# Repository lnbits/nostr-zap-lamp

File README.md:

# Nostr Zap Lamp

Get a visual "Zap!"" when someone zaps you or anyone on Nostr.

The Nostr Zap Lamp flashes when a relay broadcasts a Nostr event of kind 9735. You can set the lamp to flash zaps sent to a specific npub, or any npub on nostr.

The number of flashes corresponds to the number of digits in the number of sats sent. i.e. 3 sats will result in 1 flash, 152 sats will result in 3 flashes, 1001 sats will result in 4 flashes.

[Buy a pre-assembled or complete Zap Lamp kit on the LNbits shop](https://shop.lnbits.com/product/nostr-zap-lamp)

# Features

+ Show a signal when a zap is sent to one or all nostr npubs
+ Background brightness control
+ Easily configure to use your own nostr relay
+ Simple configuration to work with any npub

## Parts
+ [LED "Neon" lamp](https://www.amazon.co.uk/YIVIYAR-Lightning-Battery-Bedroom-Christmas/dp/B08K4SCVKQ)
+ An ESP32 dev board
+ USB cable
+ A momentary switch push button - For example https://www.amazon.com/Momentary-Spring-Return-Self-Return-Pushbutton-Switches/dp/B09DJY5Y5L
+ Four jumper cables
+ Block connectors
+ A case. [This repo includes files for a 3D printed case](enclosure)

## Build Instructions

+ Identify the positive and negative leads of the lamp. Tie a knot in the +ve lead for future identification
+ Cut the lamp leads to around 10cm long
+ Attach a female jumper lead to each. Solder or use block connectors to attach the leads.
+ Attach female jumper leads to the push button
+ Connect the lamp to the ESP32: GPIO13 on the ESP32 -> lamp's positive wire and GND on the ESP32 -> lamp's negative wire.
+ Connect the push button button to the ESP32 on GPIO4 and GND
+ Install the lamp, ESP32, button and lead in the printed enclosure
+ Power on the device and configure using the WiFi access point portal.

## Firmware Upload Instructions

+ Use the web installer at https://nostr-zap-lamp.lnbits.com/ to flash and configure the device
+ Alternatively, use the Arduino IDE to flash the firmware.
    - Install the ESP32 board in the Arduino IDE by adding the following URL to the board manager: https://dl.espressif.com/dl/package_esp32_index.json
    - Install the following libraries using the Arduino IDE library manager:
        - uBitcoin
        - WebSockets
        - ArduinoJson
        - base64
        - WiFiManager
        - Nostr
    - Open the nostrZapLamp.ino file in the Arduino IDE
    - Select the ESP32 Dev Module board and the correct port
    - Compile and upload the firmware
    - Use the web installer at https://nostr-zap-lamp.lnbits.com/ to configure the device
        
## 5v Relay option

Using a 5v Relay the lamp will be brighter, or you can swap out the light and connect anything to the relay that you want to turn on.

ESP32 GND <==========================> Relay "DC-"

ESP32 5V <==========================> Relay "DC+"

LED POS <===========================> Relay "DC+"

ESP32 GND <=========================> Relay "COM"

LED GND <===========================> Relay "NO"

GPIO 13 <===========================> Relay "S"

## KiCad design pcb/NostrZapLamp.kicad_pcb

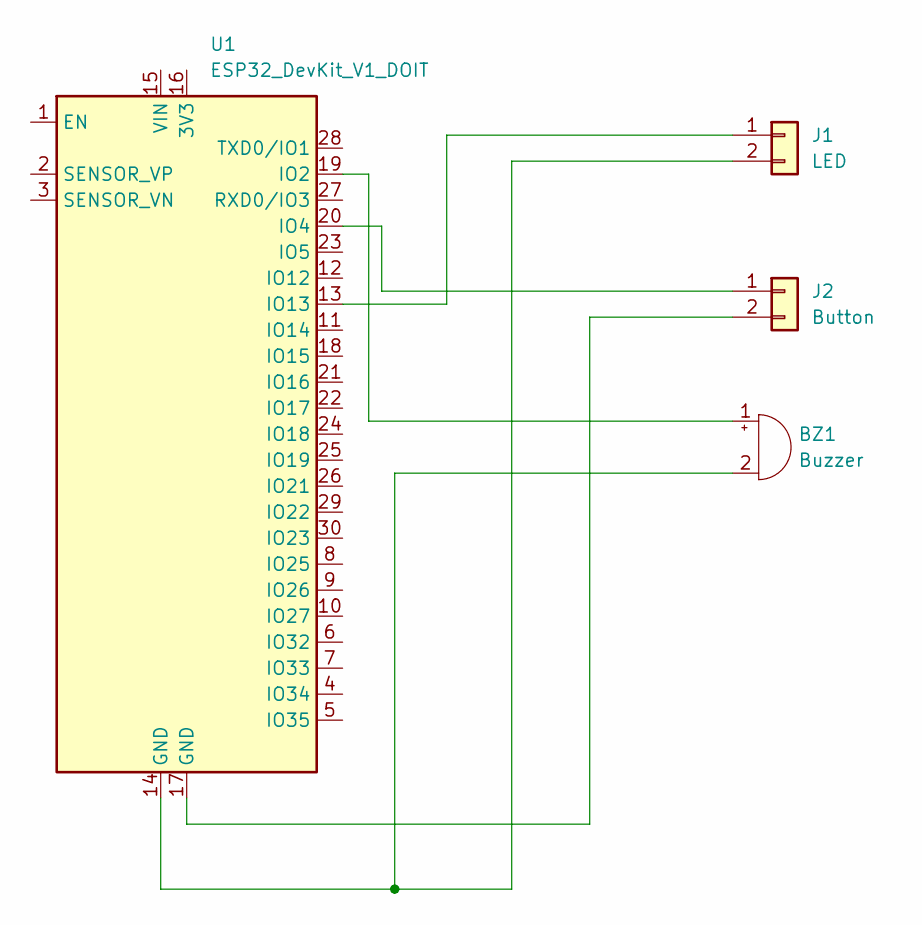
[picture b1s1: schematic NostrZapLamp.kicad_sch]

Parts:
BZ1: Buzzer; Buzzer_TDK_PS1240P02BT_D12.2mm_H6.5mm
J1: LED; PinHeader_1x02_P2.54mm_Vertical
J2: Button; PinHeader_1x02_P2.54mm_Vertical
U1: ESP32_DevKit_V1_DOIT; esp32_devkit_v1_doit

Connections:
unnamed: BZ1.2 (+), J1.2, U1.14 (GND)
unnamed: BZ1.1 (-), U1.19 (IO2)
unnamed: J1.1, U1.13 (IO13)
unnamed: J2.1, U1.20 (IO4)
unnamed: J2.2, U1.17 (GND)

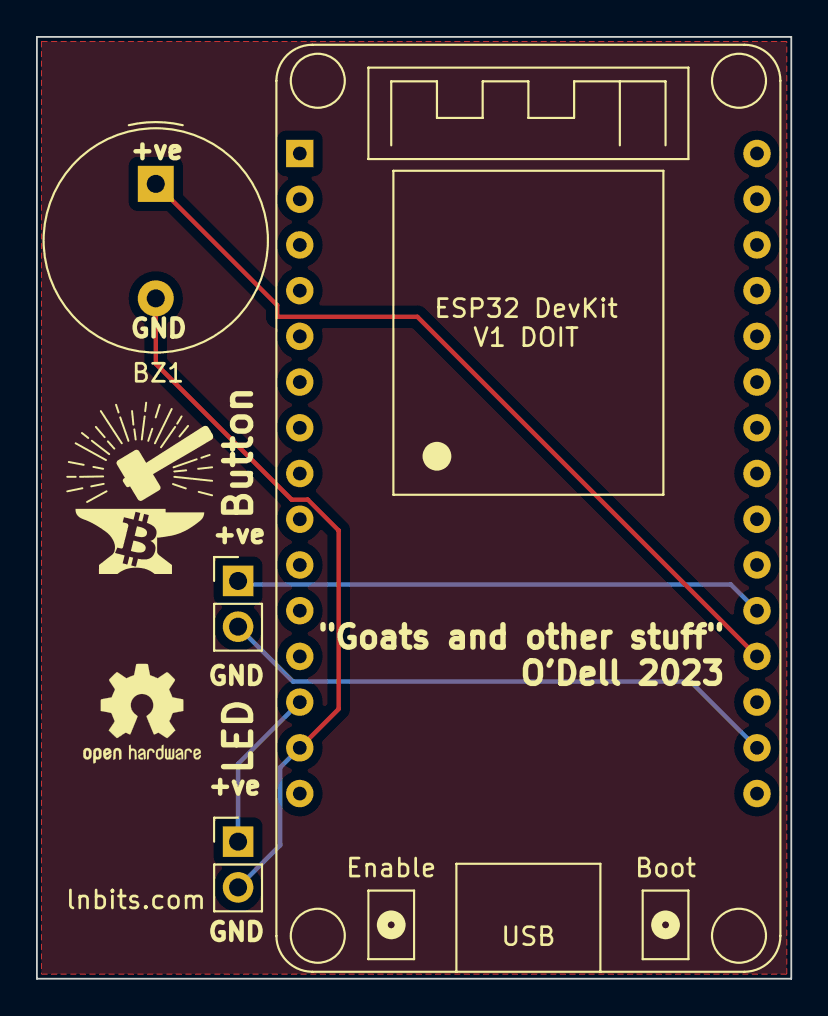
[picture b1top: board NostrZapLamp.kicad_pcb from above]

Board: 2 copper layers, 41.9 x 52.3 mm, 4 parts (0 on the bottom side), 5 nets.

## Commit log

2023-07-25 First commit;
2023-07-25 Added readme
2023-07-26 Improve lightning flash effect
2023-07-27 Added button brightness control and SPIFFs storage of setting
2023-07-27 Bug fix for npub watch in main and arduino nostr lib
2023-07-27 Auto launch AP portal on button press on boot
2023-07-27 Tweaks
2023-07-27 Adjust brightness improvements
2023-07-27 Tweeaks and added readme
2023-07-27 Added image to readme and enclosure stls
2023-07-27 Various improvements
2023-07-27 Improved internet reconnection reliability
2023-07-28 Added FreeRTOS task for lamp control. added pulse on internet connect/disconnect
2023-07-28 Working through wifi connection issues...
2023-07-28 Getting somewhere?
2023-07-28 Narly there
2023-07-28 Bug fix?
2023-07-28 Added code for wifi events
2023-07-28 All working well now. Needs tidiying up and Serial.prints removing
2023-07-29 Working properly now!
2023-07-29 Changed type of relays in NostrRelayManager to allow it to be set dynamically
2023-07-29 Work on reconnecting to relays after internet connection, but not router IP is lost
2023-07-30 Reboot on internet come back to reset all the things
2023-07-31 Stability improvements and reboot on 3 relay disconnect messages
2023-07-31 Rename relay label on AP to tell use to enter just one relay
2023-07-31 Reboot every hour to refresh relay connections
2023-08-03 Remove nostr-arduino lib from repo and moved to dependency in platformio.ini
2023-08-10 Clear wifi settings when forcing device into AP mode
2023-08-10 Added title and hostname to WM
2023-08-10 Removed unusued vars
2023-08-10 actually reboot after 3 disconnects
2023-10-04 Readme clarrity
2023-10-04 Added KiCAD PCB layouts and gerber files and reorganised the repo
2023-10-04 remove lock file
2023-10-04 Move readme to repo root
2023-10-04 PCB tweaks. Update gitignore to exclude kicad locks
2023-10-04 Ignore backups
2023-10-04 Added quote to PCB
2023-10-04 Fixed design rule check issues
2023-10-04 Updated Gerber files
2023-10-04 Added arrows for solder points to pcb
2023-10-04 Added solder masks
2023-10-04 Change PCB holes to wider spacing for buzzer
2023-10-09 Added buzzer on pin 2
2023-10-09 Added buzzer click on zap event.
2023-10-09 Addded buzzer disable bool flag
2023-10-30 huge commit :)
2023-10-30 add verions
2023-10-30 remove app0
2023-10-30 prod build
2023-10-30 add hardware-installer, github arduino workflows, release workflows (#10)
    moved code/ to nostrZapLamp
    renamed main.cpp to nostrZapLamp.ino
2023-10-30 [CHORE] update version to v0.0.1
2023-10-30 Removed wManager and unused libs (QRCode ESP32Ping
2023-10-30 fix: build workflows
2023-10-30 add build properties
2023-10-30 fixup!
2023-10-30 fix: build workflows (#11)
2023-10-30 fixup! (#12)
2023-10-30 Added serial config
2023-10-30 Removed commented out code
2023-10-30 Added function comments
2023-10-30 Move img to root dir
2023-10-30 Remove web server
2023-10-30 replace sitetitle placeholder
2023-10-30 Fixes for build
2023-10-30 replace sitetitle placeholder (#14)
2023-10-30 Remove code dir
2023-10-30 Renamed config vars to config_*
2023-10-30 Renamed config vars to config_* (#16)
2023-10-30 fix: path for firmware
2023-10-30 add label to versions.json
2023-10-30 remove static from release workflow
2023-10-30 remove duplicate version
2023-10-30 Bug fix for config launch
2023-10-31 remove hero
2023-10-31 add readme to deploy
2023-10-31 update image path
2023-10-31 Various refactoring and bug fixes
2023-10-31 Various tweaks for configuration mode
2023-10-31 Reduce inital brightness
2023-10-31 Added fun phrases for zap receipts
2023-10-31 add installer.md
2023-10-31 Remove wifi connection state set in loop
2023-10-31 Various refactoring and bug fixes (#18)
    * Various refactoring and bug fixes
    * Various tweaks for configuration mode
    * Reduce inital brightness
    * Added fun phrases for zap receipts
    * Remove wifi connection state set in loop
2023-10-31 [CHORE] update version to v0.0.2
2023-10-31 Fix typos in installer.md
2023-10-31 Fix Wifi connection timeout bug
2023-10-31 [CHORE] update version to v0.0.3
2023-10-31 Remove serial from get random number
2023-10-31 Made serial prints more user friendly
2023-10-31 Updated readme with instructions for web configurator
2024-04-19 Webinstaller URL
2024-04-19 Webinstaller URL fixed (#24)
    * Webinstaller URL
    * Update README.md
2024-08-21 We should just turn the thing on/off
    Like the switch, could be used to zap and turn things on, rather than falshing
2024-08-22 Added var for duration
2024-11-06 fix: build was broken for esp 3.x.x (uBitcoin incompatible)
    fix to version 2.0.17
2024-11-06 fix workflow
2024-11-06 fix esp version in workflow
2024-11-06 fix: build was broken for esp 3.x.x (uBitcoin incompatible) (#28)
    * fix: build was broken for esp 3.x.x (uBitcoin incompatible)
    fix to version 2.0.17
    * fix workflow
    * fix esp version in workflow
2025-07-29 feat: new webinstaller and bootmode
2025-08-24 release workflows
